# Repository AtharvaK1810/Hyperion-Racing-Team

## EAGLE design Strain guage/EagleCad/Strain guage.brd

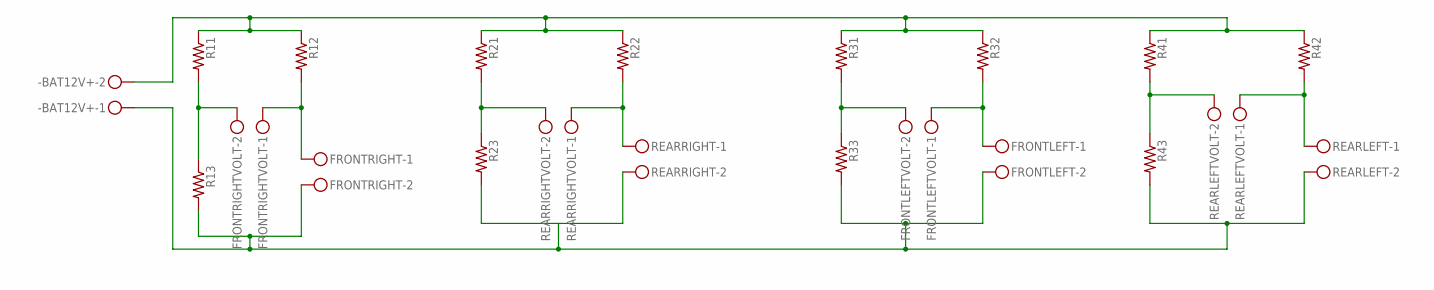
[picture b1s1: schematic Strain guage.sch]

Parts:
-BAT12V+: MKDSN1,5/2-5,08
FRONTLEFT: MKDSN1,5/2-5,08
FRONTLEFTVOLT: MKDSN1,5/2-5,08
FRONTRIGHT: MKDSN1,5/2-5,08
FRONTRIGHTVOLT: MKDSN1,5/2-5,08
R11, R12, R13, R21, R22, R23, R31, R32, R33, R41, R42, R43: R-US_0204/7; 0204/7
REARLEFT: MKDSN1,5/2-5,08
REARLEFTVOLT: MKDSN1,5/2-5,08
REARRIGHT: MKDSN1,5/2-5,08
REARRIGHTVOLT: MKDSN1,5/2-5,08

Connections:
unnamed: -BAT12V+.2, R11.1, R12.1, R21.1, R22.1, R31.1, R32.1, R41.1, R42.1
unnamed: FRONTRIGHTVOLT.2, R11.2, R13.1
unnamed: -BAT12V+.1, FRONTLEFT.2, FRONTRIGHT.2, R13.2, R23.2, R33.2, R43.2, REARLEFT.2, REARRIGHT.2
unnamed: FRONTRIGHT.1, FRONTRIGHTVOLT.1, R12.2
unnamed: R21.2, R23.1, REARRIGHTVOLT.2
unnamed: R22.2, REARRIGHT.1, REARRIGHTVOLT.1
unnamed: FRONTLEFTVOLT.2, R31.2, R33.1
unnamed: FRONTLEFT.1, FRONTLEFTVOLT.1, R32.2
unnamed: R41.2, R43.1, REARLEFTVOLT.2
unnamed: R42.2, REARLEFT.1, REARLEFTVOLT.1

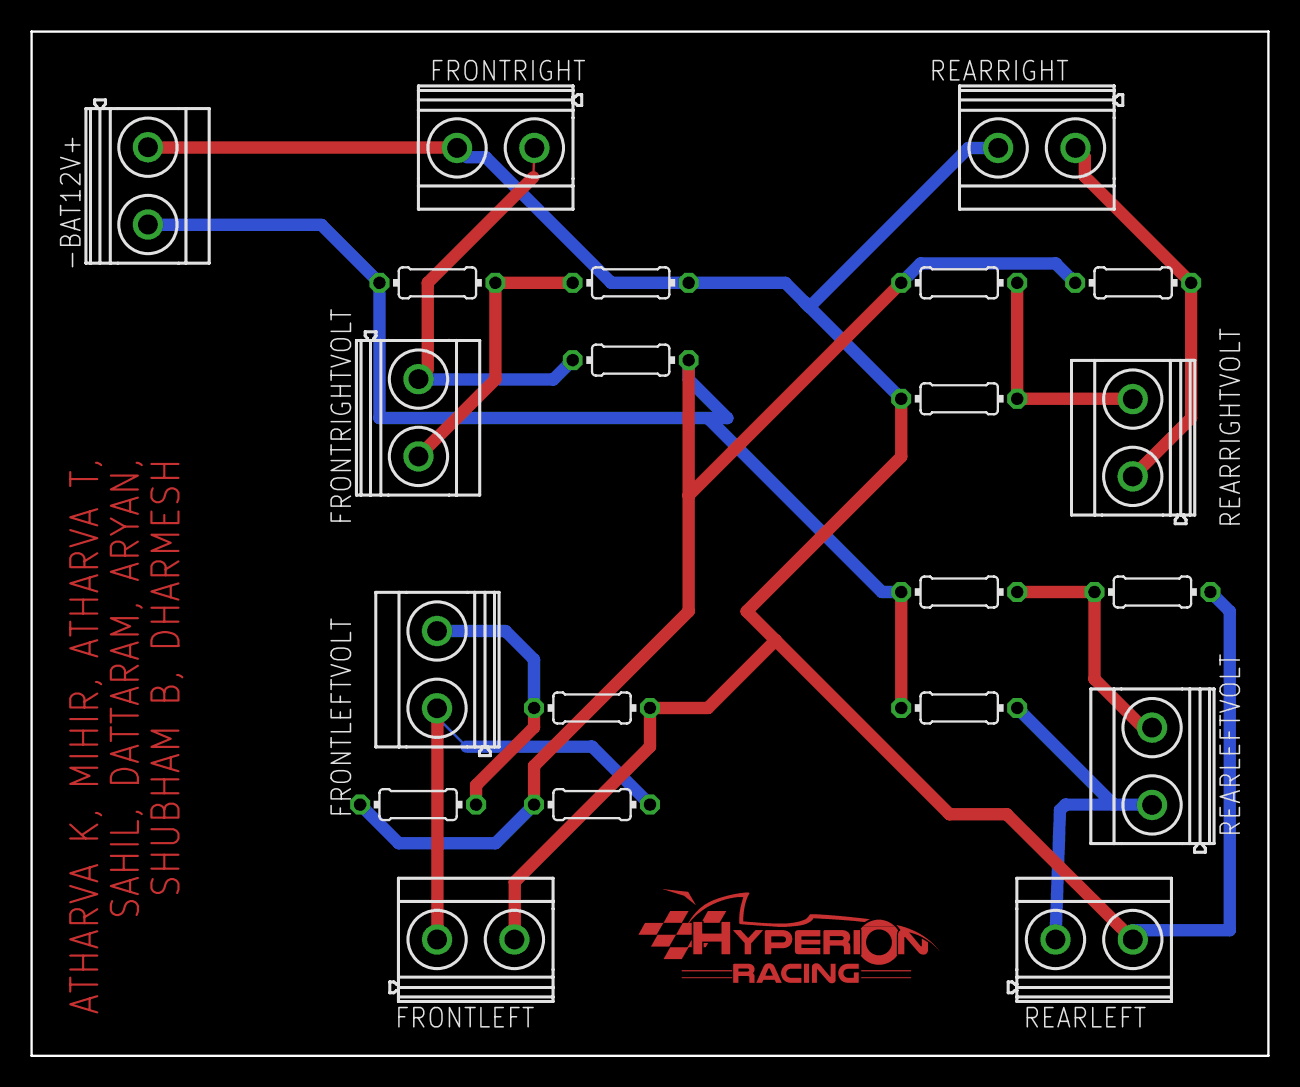
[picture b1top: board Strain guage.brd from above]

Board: 2 copper layers, 81.3 x 67.3 mm, 21 parts (0 on the bottom side), 10 nets.

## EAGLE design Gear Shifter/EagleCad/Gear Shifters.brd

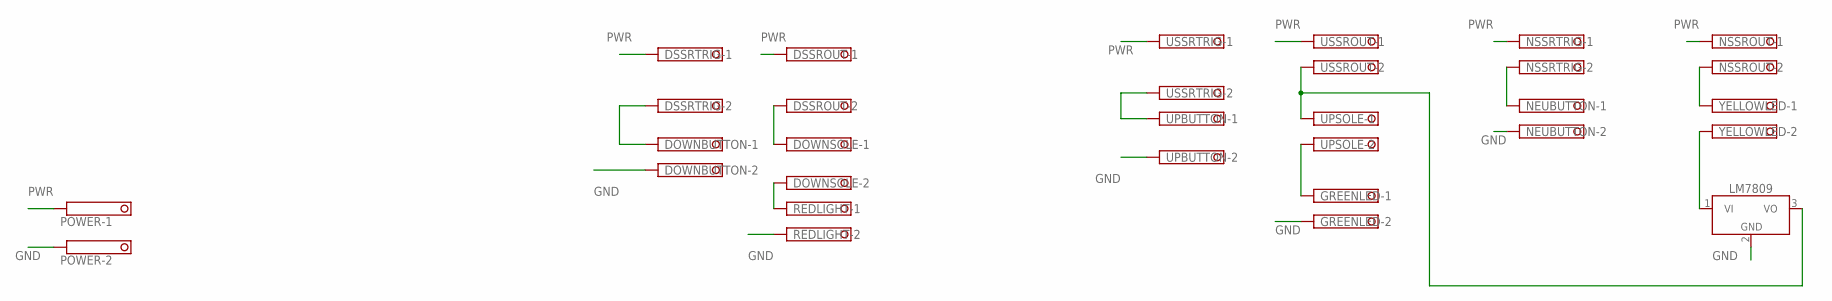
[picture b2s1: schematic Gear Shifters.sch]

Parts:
DOWNBUTTON: TERMINAL-BLOCK-3.5MM-2-PIN-ROUND-PAD; TERMINAL-BLOCK-2-PIN-3.5MM-ROUND-PAD
DOWNSOLE: TERMINAL-BLOCK-3.5MM-2-PIN-ROUND-PAD; TERMINAL-BLOCK-2-PIN-3.5MM-ROUND-PAD
DSSROUT: TERMINAL-BLOCK-3.5MM-2-PIN-ROUND-PAD; TERMINAL-BLOCK-2-PIN-3.5MM-ROUND-PAD
DSSRTRIG: TERMINAL-BLOCK-3.5MM-2-PIN-ROUND-PAD; TERMINAL-BLOCK-2-PIN-3.5MM-ROUND-PAD
GREENLED: TERMINAL-BLOCK-3.5MM-2-PIN-ROUND-PAD; TERMINAL-BLOCK-2-PIN-3.5MM-ROUND-PAD
LM7809: LM7805_TO220V; TO220V
NEUBUTTON: TERMINAL-BLOCK-3.5MM-2-PIN-ROUND-PAD; TERMINAL-BLOCK-2-PIN-3.5MM-ROUND-PAD
NSSROUT: TERMINAL-BLOCK-3.5MM-2-PIN-ROUND-PAD; TERMINAL-BLOCK-2-PIN-3.5MM-ROUND-PAD
NSSRTRIG: TERMINAL-BLOCK-3.5MM-2-PIN-ROUND-PAD; TERMINAL-BLOCK-2-PIN-3.5MM-ROUND-PAD
POWER: TERMINAL-BLOCK-3.5MM-2-PIN-ROUND-PAD; TERMINAL-BLOCK-2-PIN-3.5MM-ROUND-PAD
REDLIGHT: TERMINAL-BLOCK-3.5MM-2-PIN-ROUND-PAD; TERMINAL-BLOCK-2-PIN-3.5MM-ROUND-PAD
UPBUTTON: TERMINAL-BLOCK-3.5MM-2-PIN-ROUND-PAD; TERMINAL-BLOCK-2-PIN-3.5MM-ROUND-PAD
UPSOLE: TERMINAL-BLOCK-3.5MM-2-PIN-ROUND-PAD; TERMINAL-BLOCK-2-PIN-3.5MM-ROUND-PAD
USSROUT: TERMINAL-BLOCK-3.5MM-2-PIN-ROUND-PAD; TERMINAL-BLOCK-2-PIN-3.5MM-ROUND-PAD
USSRTRIG: TERMINAL-BLOCK-3.5MM-2-PIN-ROUND-PAD; TERMINAL-BLOCK-2-PIN-3.5MM-ROUND-PAD
YELLOWLED: TERMINAL-BLOCK-3.5MM-2-PIN-ROUND-PAD; TERMINAL-BLOCK-2-PIN-3.5MM-ROUND-PAD

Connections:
GND: DOWNBUTTON.2, GREENLED.2, LM7809.2 (GND), NEUBUTTON.2, POWER.2, REDLIGHT.2, UPBUTTON.2
unnamed: DOWNBUTTON.1, DSSRTRIG.2
unnamed: DOWNSOLE.1, DSSROUT.2
unnamed: UPBUTTON.1, USSRTRIG.2
unnamed: DOWNSOLE.2, REDLIGHT.1
unnamed: NEUBUTTON.1, NSSRTRIG.2
unnamed: NSSROUT.2, YELLOWLED.1
unnamed: LM7809.1 (VI), YELLOWLED.2
unnamed: LM7809.3 (VO), UPSOLE.1, USSROUT.2
unnamed: GREENLED.1, UPSOLE.2
PWR: DSSROUT.1, DSSRTRIG.1, NSSROUT.1, NSSRTRIG.1, POWER.1, USSROUT.1, USSRTRIG.1

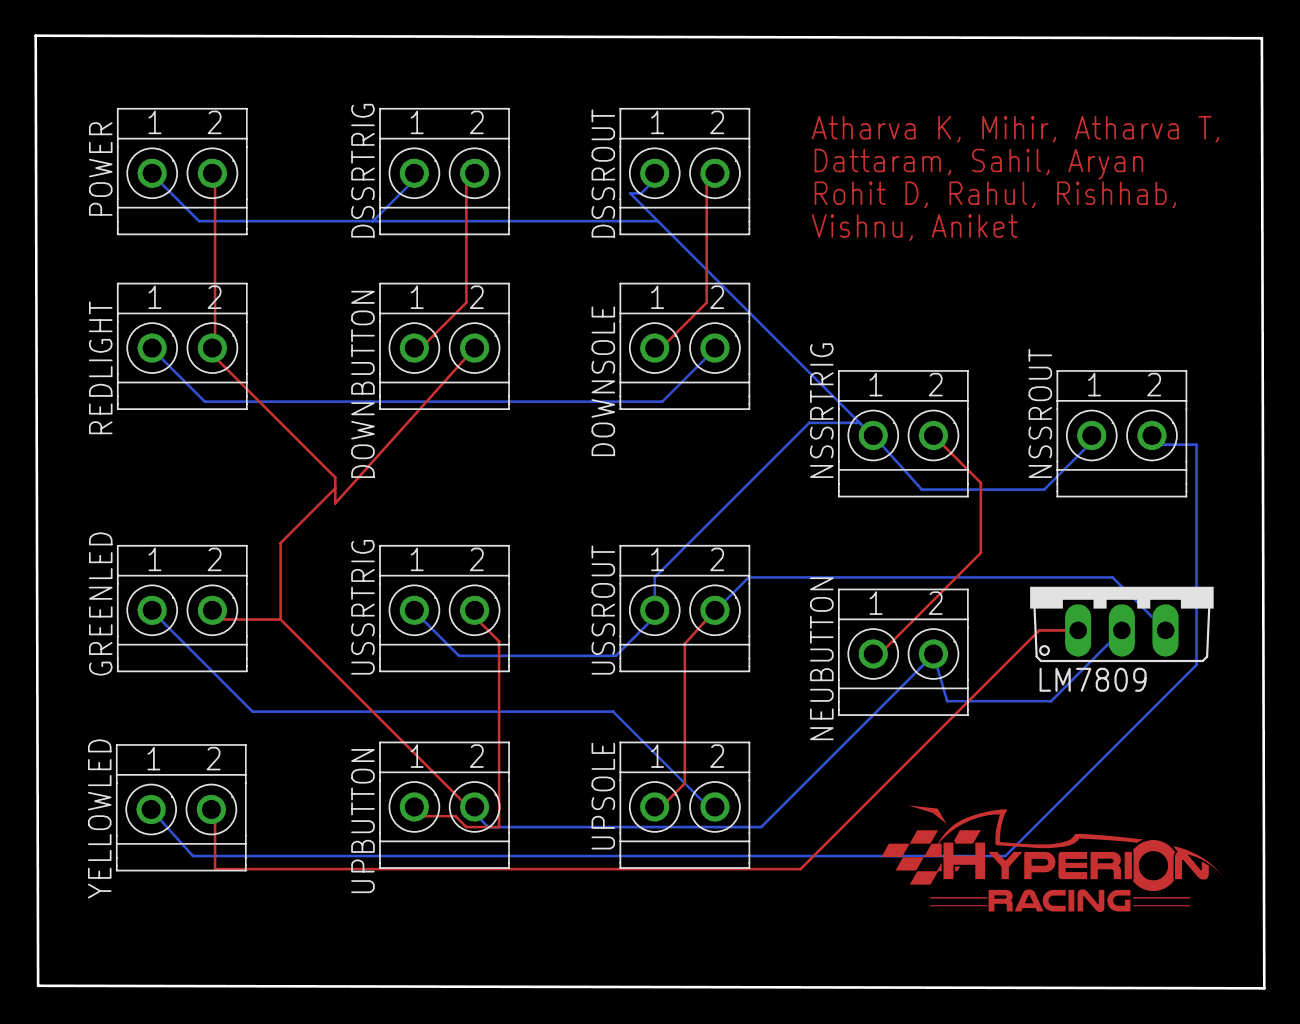
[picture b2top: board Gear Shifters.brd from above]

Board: 2 copper layers, 71.4 x 55.4 mm, 16 parts (0 on the bottom side), 11 nets.

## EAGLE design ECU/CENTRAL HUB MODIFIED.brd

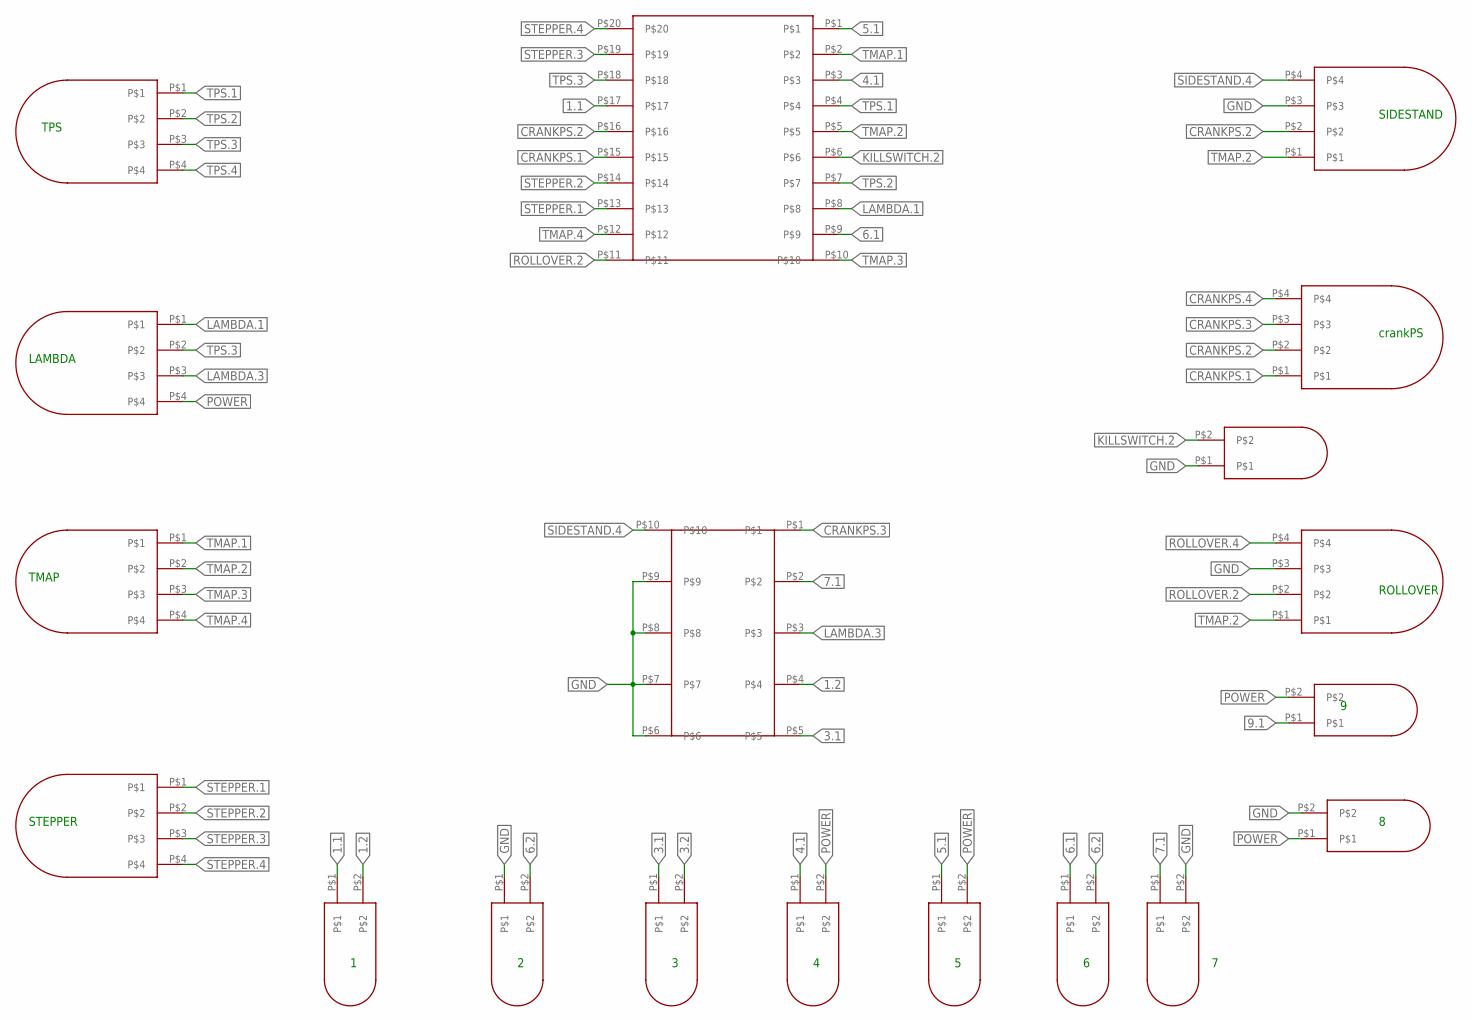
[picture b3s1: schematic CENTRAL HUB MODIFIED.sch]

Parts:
1, 2, 3, 4, 5, 6, 7, 8, 9: 2-PIN; 2PIN
CRANK: 4-PIN; 4PIN
KILLSWITCH: 2-PIN; 2PIN
LAMBDA: 4-PIN; 4PIN
ROLLOVER: 4-PIN; 4PIN
SIDESTAND: 4-PIN; 4PIN
STEPPER: 4-PIN; 4PIN
TMAP: 4-PIN; 4PIN
TPS: 4-PIN; 4PIN
U$1: ECU1-20; ECU
U$2: ECU2-10; 10PIN

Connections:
1.1: 1.P$1, U$1.P$17
1.2: 1.P$2, U$2.P$4
3.1: 3.P$1, U$2.P$5
3.2: 3.P$2
4.1: 4.P$1, U$1.P$3
5.1: 5.P$1, U$1.P$1
6.1: 6.P$1, U$1.P$9
6.2: 2.P$2, 6.P$2
7.1: 7.P$1, U$2.P$2
9.1: 9.P$1
CRANKPS.1: CRANK.P$1, U$1.P$15
CRANKPS.2: CRANK.P$2, SIDESTAND.P$2, U$1.P$16
CRANKPS.3: CRANK.P$3, U$2.P$1
CRANKPS.4: CRANK.P$4
GND: 2.P$1, 7.P$2, 8.P$2, KILLSWITCH.P$1, ROLLOVER.P$3, SIDESTAND.P$3, U$2.P$6, U$2.P$7, U$2.P$8, U$2.P$9
KILLSWITCH.2: KILLSWITCH.P$2, U$1.P$6
LAMBDA.1: LAMBDA.P$1, U$1.P$8
LAMBDA.3: LAMBDA.P$3, U$2.P$3
POWER: 4.P$2, 5.P$2, 8.P$1, 9.P$2, LAMBDA.P$4
ROLLOVER.2: ROLLOVER.P$2, U$1.P$11
ROLLOVER.4: ROLLOVER.P$4
SIDESTAND.4: SIDESTAND.P$4, U$2.P$10
STEPPER.1: STEPPER.P$1, U$1.P$13
STEPPER.2: STEPPER.P$2, U$1.P$14
STEPPER.3: STEPPER.P$3, U$1.P$19
STEPPER.4: STEPPER.P$4, U$1.P$20
TMAP.1: TMAP.P$1, U$1.P$2
TMAP.2: ROLLOVER.P$1, SIDESTAND.P$1, TMAP.P$2, U$1.P$5
TMAP.3: TMAP.P$3, U$1.P$10
TMAP.4: TMAP.P$4, U$1.P$12
TPS.1: TPS.P$1, U$1.P$4
TPS.2: TPS.P$2, U$1.P$7
TPS.3: LAMBDA.P$2, TPS.P$3, U$1.P$18
TPS.4: TPS.P$4

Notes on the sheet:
TPS
LAMBDA
TMAP
STEPPER
SIDESTAND
crankPS
ROLLOVER

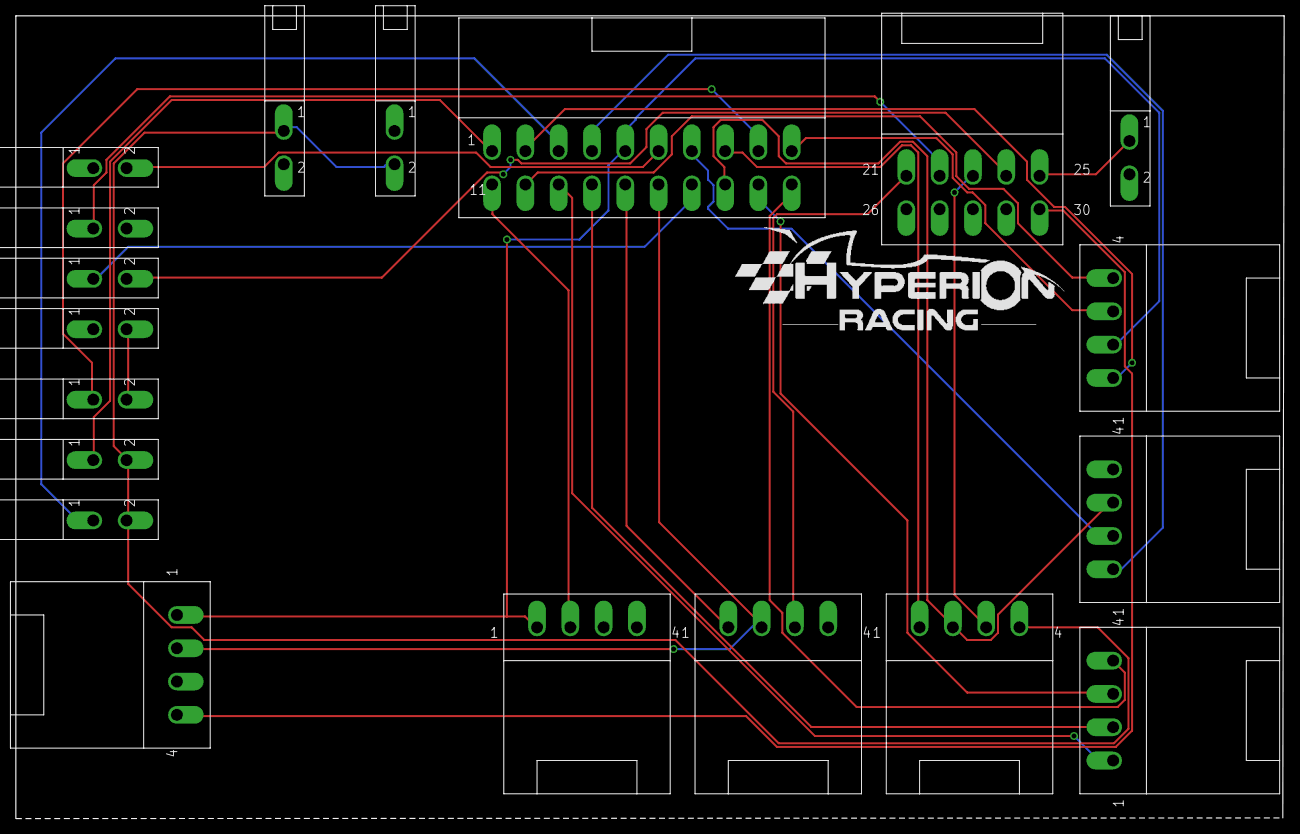
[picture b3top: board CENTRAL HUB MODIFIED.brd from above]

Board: 2 copper layers, 160.0 x 101.3 mm, 19 parts (0 on the bottom side), 29 nets.

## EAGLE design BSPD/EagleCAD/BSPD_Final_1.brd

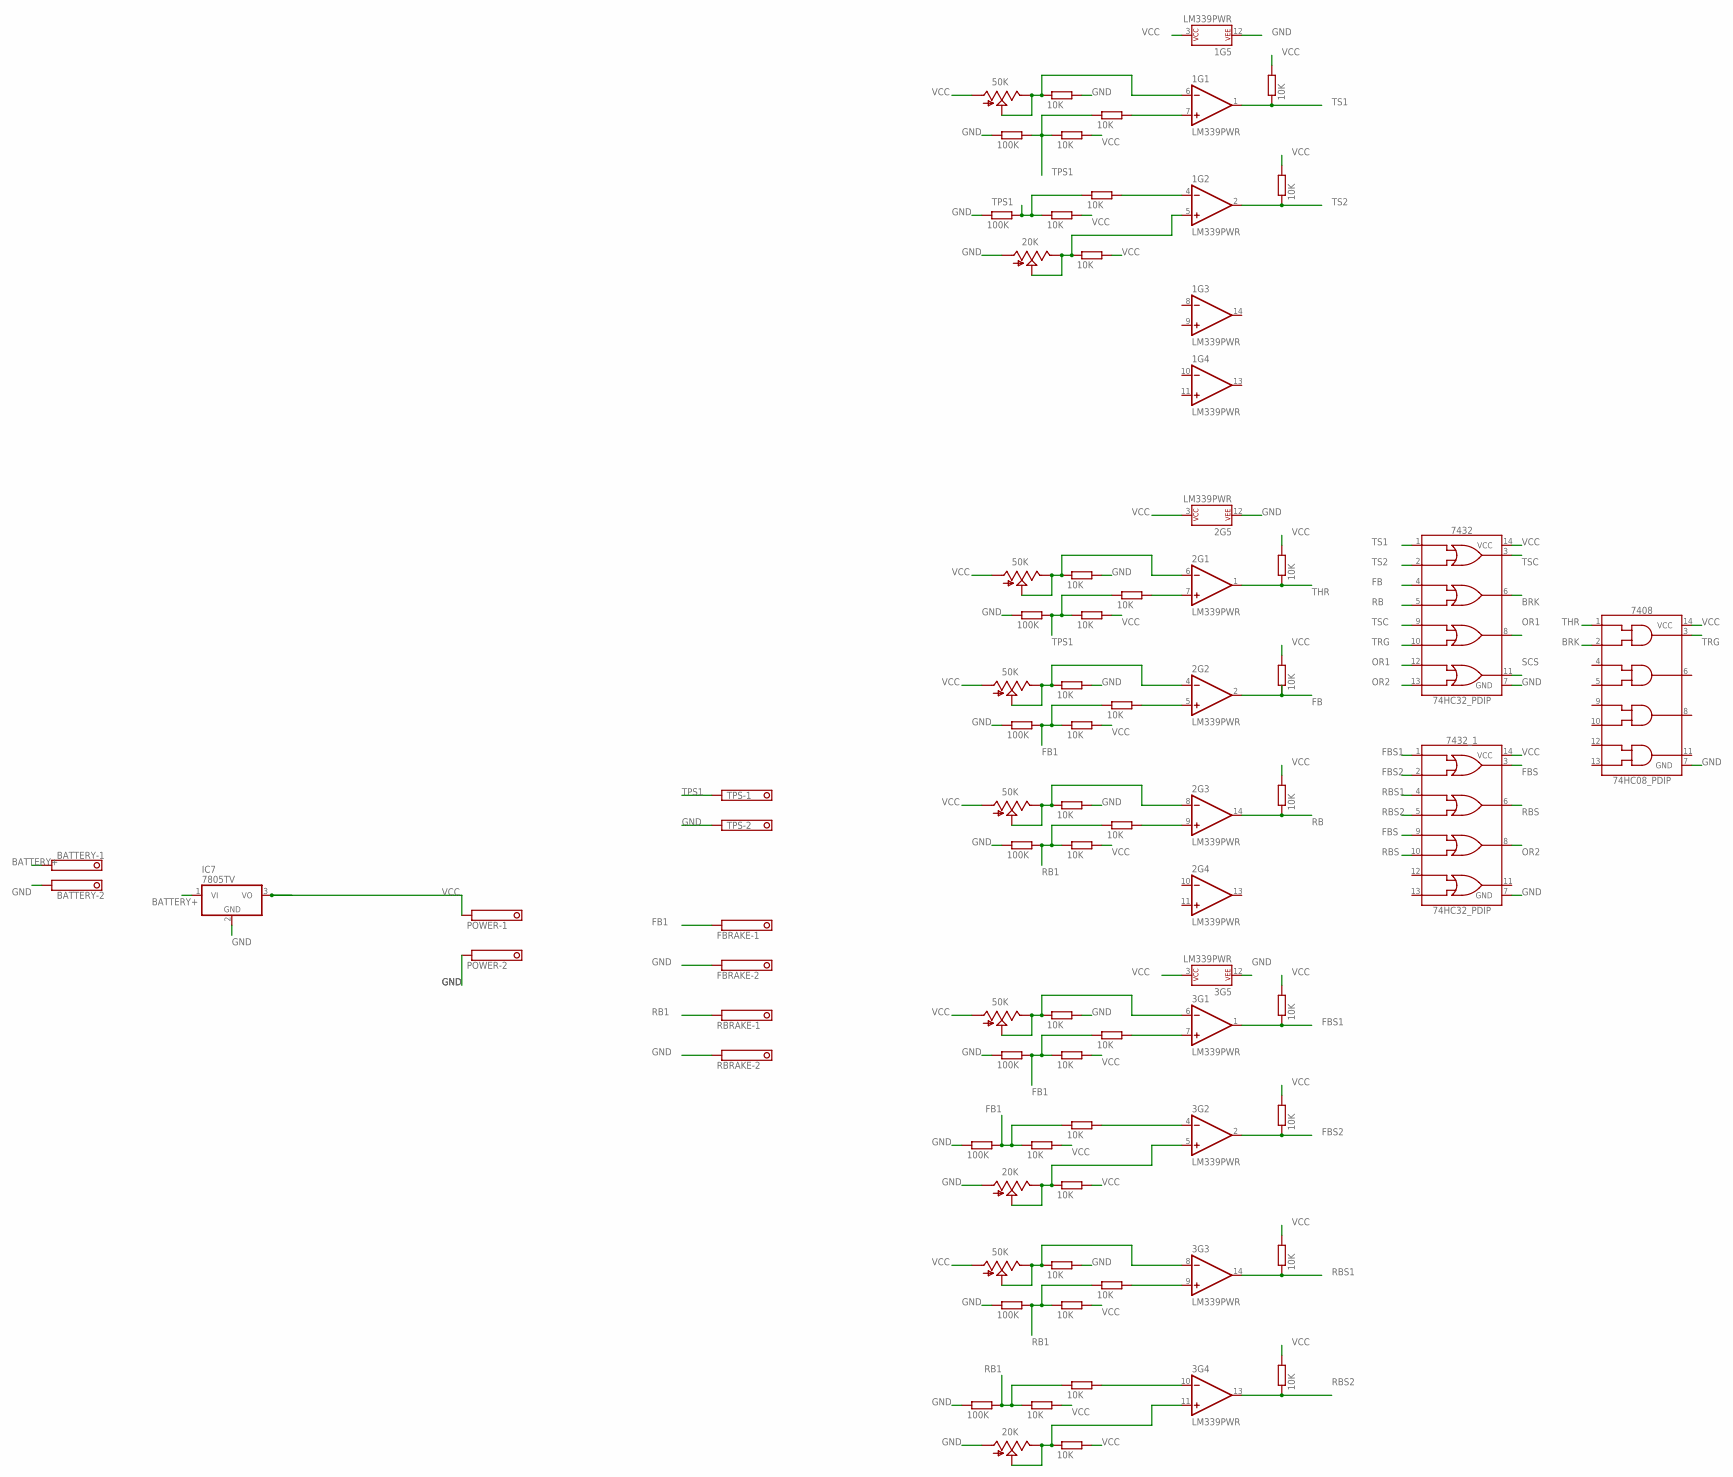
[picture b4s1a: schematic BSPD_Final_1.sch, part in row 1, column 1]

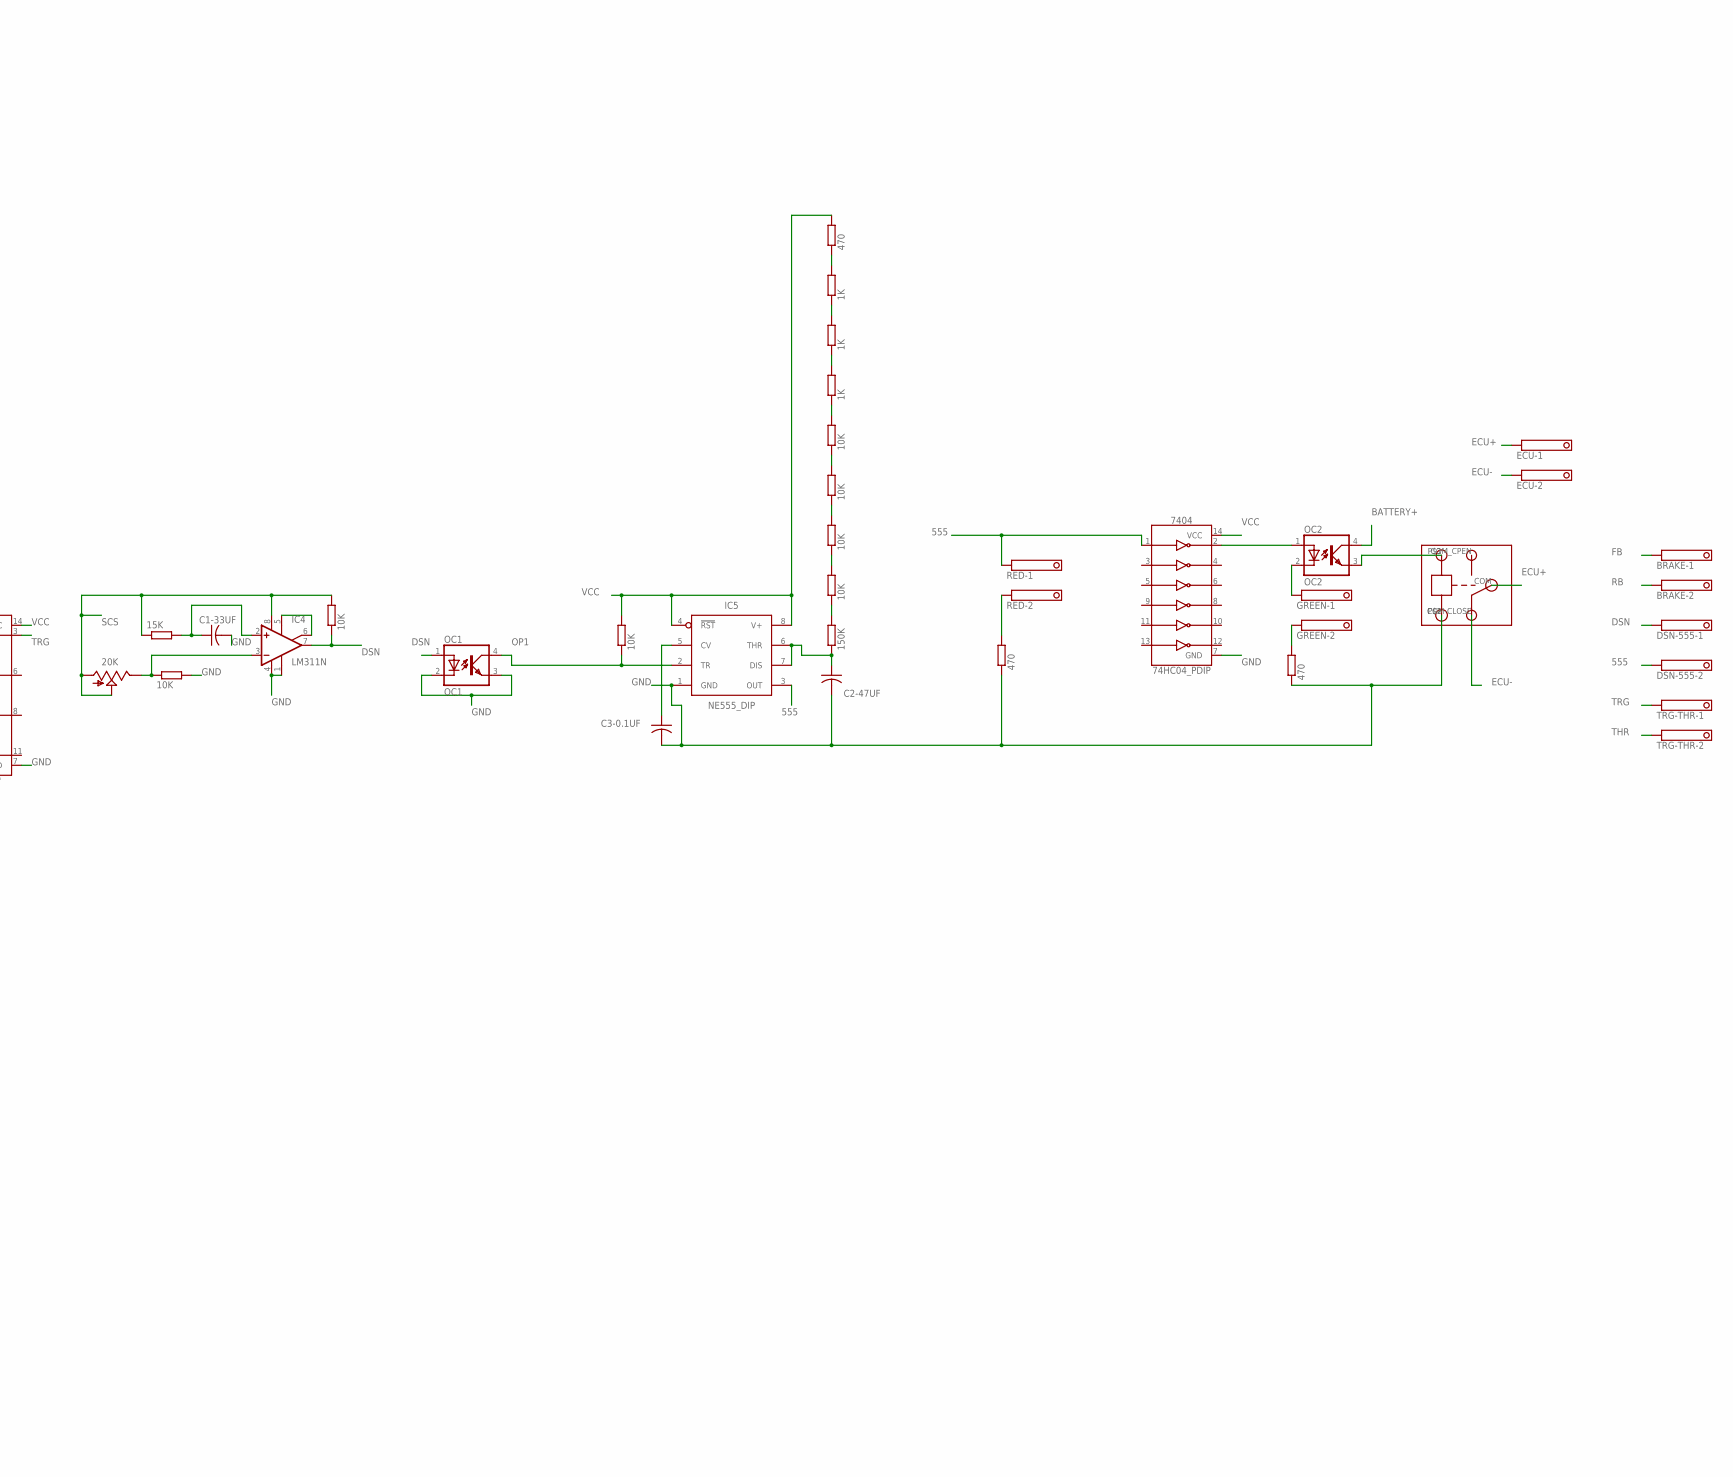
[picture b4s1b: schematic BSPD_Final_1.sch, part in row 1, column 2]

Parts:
1, 2, 3: LM339PWR; TSSOP-14
50K9: 20K; B64Y
555RES1: 150K; 0207/10
555RES2, 555RES3, 555RES4, 555RES5: 10K; 0207/10
555RES6, 555RES7, 555RES8: 1K; 0207/10
555RES9: 470; 0207/10
7404: 74HC04_PDIP; DIP762W53P254L1969H508Q14B
7408: 74HC08_PDIP; DIP762W53P254L1969H508Q14B
7432, 7432_1: 74HC32_PDIP; DIP762W53P254L1969H508Q14B
BATTERY: TERMINAL-BLOCK-3.5MM-2-PIN-ROUND-PAD; TERMINAL-BLOCK-2-PIN-3.5MM-ROUND-PAD
BRAKE: TERMINAL-BLOCK-3.5MM-2-PIN-ROUND-PAD; TERMINAL-BLOCK-2-PIN-3.5MM-ROUND-PAD
C1-33UF, C2-47UF, C3-0.1UF: 33uF; CAP_RADIAL_2MM
DCNPULL: 10K; 0207/10
DCNRES1: 15K; 0207/10
DCNRES2: 10K; 0207/10
DSN-555: TERMINAL-BLOCK-3.5MM-2-PIN-ROUND-PAD; TERMINAL-BLOCK-2-PIN-3.5MM-ROUND-PAD
ECU: TERMINAL-BLOCK-3.5MM-2-PIN-ROUND-PAD; TERMINAL-BLOCK-2-PIN-3.5MM-ROUND-PAD
FBRAKE: TERMINAL-BLOCK-3.5MM-2-PIN-ROUND-PAD; TERMINAL-BLOCK-2-PIN-3.5MM-ROUND-PAD
GREEN: TERMINAL-BLOCK-3.5MM-2-PIN-ROUND-PAD; TERMINAL-BLOCK-2-PIN-3.5MM-ROUND-PAD
IC4: LM311N; DIL08
IC5: NE555_DIP; DIP826W53P254L959H508Q8B
IC7: 7805TV; TO220V
OC1: OC1; DIL04
OC2: OC2; DIL04
OCTPULL: 10K; 0207/10
POT1, POT3, POT4, POT5, POT6, POT8: 50K; B64Y
POT2, POT7, POT9: 20K; B64Y
POWER: TERMINAL-BLOCK-3.5MM-2-PIN-ROUND-PAD; TERMINAL-BLOCK-2-PIN-3.5MM-ROUND-PAD
PULL1, PULL2, PULL3, PULL4, PULL5, PULL6, PULL7, PULL8, PULL9: 10K; 0207/10
R56, R57: 470; 0207/10
RBRAKE: TERMINAL-BLOCK-3.5MM-2-PIN-ROUND-PAD; TERMINAL-BLOCK-2-PIN-3.5MM-ROUND-PAD
RED: TERMINAL-BLOCK-3.5MM-2-PIN-ROUND-PAD; TERMINAL-BLOCK-2-PIN-3.5MM-ROUND-PAD
RES11, RES12, RES14, RES21, RES22, RES23, RES31, RES32, RES34, RES41, RES42, RES44, RES51, RES52, RES54, RES61, RES62, RES64, RES71, RES72, RES74, RES81, RES82, RES84, RES91, RES92, RES94: 10K; 0207/10
RES13, RES24, RES33, RES43, RES53, RES63, RES73, RES83, RES93: 100K; 0207/10
TPS: TERMINAL-BLOCK-3.5MM-2-PIN-ROUND-PAD; TERMINAL-BLOCK-2-PIN-3.5MM-ROUND-PAD
TRG-THR: TERMINAL-BLOCK-3.5MM-2-PIN-ROUND-PAD; TERMINAL-BLOCK-2-PIN-3.5MM-ROUND-PAD
U$1: RELAY

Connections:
555: 7404.1 (1A), DSN-555.2, IC5.3 (OUT), RED.1
BATTERY+: BATTERY.1, IC7.1 (VI), OC2.4 (COL)
BRK: 7408.2 (1B), 7432.6 (2Y)
DSN: DCNPULL.1, DSN-555.1, IC4.7 (OUT), OC1.1 (A)
ECU+: ECU.1, U$1.COM
ECU-: ECU.2, U$1.COM-CLOSE
FB: 2.2 (OUT), 7432.4 (2A), BRAKE.1, PULL4.1
FB1: FBRAKE.1, RES41.1, RES42.1, RES43.2, RES61.1, RES62.1, RES63.2, RES71.1, RES72.1, RES73.2
FBS: 7432_1.3 (1Y), 7432_1.9 (3A)
FBS1: 3.1 (OUT), 7432_1.1 (1A), PULL6.1
FBS2: 3.2 (OUT), 7432_1.2 (1B), PULL7.1
GND: 1.12 (P$V-), 2.12 (P$V-), 3.12 (P$V-), 7404.7 (GND), 7408.7 (GND), 7432.7 (GND), 7432_1.7 (GND), BATTERY.2, C1-33UF.2, C2-47UF.2, C3-0.1UF.2, DCNRES2.2, FBRAKE.2, IC4.1 (GND), IC4.4 (V-), IC5.1 (GND), IC7.2 (GND), OC1.2 (C), OC1.3 (EMIT), POT2.A, POT7.A, POT9.A, POWER.2, R56.1, R57.1, RBRAKE.2, RES13.1, RES14.2, RES24.1, RES33.1, RES34.2, RES43.1, RES44.2, RES53.1, RES54.2, RES63.1, RES64.2, RES73.1, RES83.1, RES84.2, RES93.1, TPS.2, U$1.P$2 (GND)
unnamed: 2.7 (+IN), RES31.2
unnamed: IC4.5 (ON), IC4.6 (ON/STR)
unnamed: 2.6 (-IN), POT3.E, POT3.S, RES34.1
unnamed: 2.5 (+IN), RES41.2
unnamed: 2.4 (-IN), POT4.E, POT4.S, RES44.1
unnamed: R56.2, RED.2
unnamed: 2.9 (+IN), RES51.2
unnamed: 2.8 (-IN), POT5.E, POT5.S, RES54.1
unnamed: C1-33UF.1, DCNRES1.2, IC4.2 (+IN)
unnamed: 3.7 (+IN), RES61.2
unnamed: 3.6 (-IN), POT6.E, POT6.S, RES64.1
unnamed: 50K9.E, DCNRES2.1, IC4.3 (-IN)
unnamed: 3.9 (+IN), RES81.2
unnamed: 3.8 (-IN), POT8.E, POT8.S, RES84.1
unnamed: C3-0.1UF.1, IC5.5 (CV)
unnamed: 1.7 (+IN), RES11.2
unnamed: 1.6 (-IN), POT1.E, POT1.S, RES14.1
unnamed: 1.4 (-IN), RES21.2
unnamed: 1.5 (+IN), POT2.E, POT2.S, RES23.1
unnamed: 555RES1.2, 555RES2.1
unnamed: 3.4 (-IN), RES71.2
unnamed: 555RES2.2, 555RES3.1
unnamed: 3.5 (+IN), POT7.E, POT7.S, RES74.1
unnamed: 555RES3.2, 555RES4.1
unnamed: 3.10 (-IN), RES91.2
unnamed: 555RES4.2, 555RES5.1
unnamed: 3.11 (+IN), POT9.E, POT9.S, RES94.1
unnamed: 555RES5.2, 555RES6.1
unnamed: GREEN.2, R57.2
unnamed: 7404.2 (1Y), OC2.1 (A)
unnamed: GREEN.1, OC2.2 (C)
unnamed: OC2.3 (EMIT), U$1.P$1 (IN)
unnamed: 555RES8.2, 555RES9.1
unnamed: 555RES7.2, 555RES8.1
unnamed: 555RES6.2, 555RES7.1
unnamed: 555RES1.1, C2-47UF.1, IC5.6 (THR), IC5.7 (DIS)
OP1: IC5.2 (TR), OC1.4 (COL), OCTPULL.1
OR1: 7432.8 (3Y), 7432.12 (4A)
OR2: 7432.13 (4B), 7432_1.8 (3Y)
RB: 2.14 (OUT), 7432.5 (2B), BRAKE.2, PULL5.1
RB1: RBRAKE.1, RES51.1, RES52.1, RES53.2, RES81.1, RES82.1, RES83.2, RES91.1, RES92.1, RES93.2
RBS: 7432_1.6 (2Y), 7432_1.10 (3B)
RBS1: 3.14 (OUT), 7432_1.4 (2A), PULL8.1
RBS2: 3.13 (OUT), 7432_1.5 (2B), PULL9.1
SCS: 50K9.A, 50K9.S, 7432.11 (4Y), DCNPULL.2, DCNRES1.1, IC4.8 (V+)
THR: 2.1 (OUT), 7408.1 (1A), PULL3.1, TRG-THR.2
TPS1: RES11.1, RES12.1, RES13.2, RES21.1, RES22.1, RES24.2, RES31.1, RES32.1, RES33.2, TPS.1
TRG: 7408.3 (1Y), 7432.10 (3B), TRG-THR.1
TS1: 1.1 (OUT), 7432.1 (1A), PULL1.1
TS2: 1.2 (OUT), 7432.2 (1B), PULL2.1
TSC: 7432.3 (1Y), 7432.9 (3A)
VCC: 1.3 (P$V+), 2.3 (P$V+), 3.3 (P$V+), 555RES9.2, 7404.14 (VCC), 7408.14 (VCC), 7432.14 (VCC), 7432_1.14 (VCC), IC5.4 (!RST), IC5.8 (V+), IC7.3 (VO), OCTPULL.2, POT1.A, POT3.A, POT4.A, POT5.A, POT6.A, POT8.A, POWER.1, PULL1.2, PULL2.2, PULL3.2, PULL4.2, PULL5.2, PULL6.2, PULL7.2, PULL8.2, PULL9.2, RES12.2, RES22.2, RES23.2, RES32.2, RES42.2, RES52.2, RES62.2, RES72.2, RES74.2, RES82.2, RES92.2, RES94.2

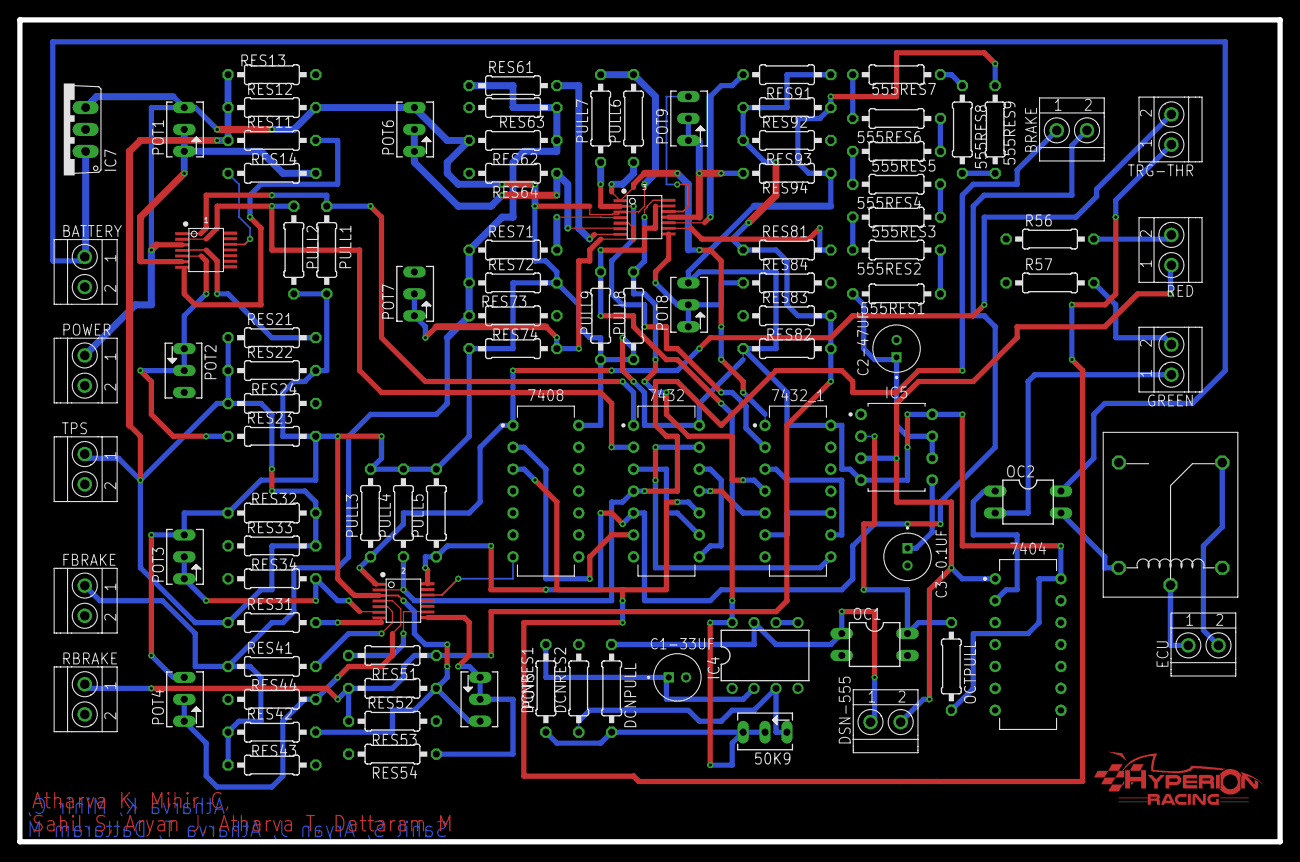
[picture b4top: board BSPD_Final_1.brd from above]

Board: 2 copper layers, 146.1 x 95.2 mm, 97 parts (0 on the bottom side), 64 nets.

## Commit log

2025-11-23 Create temp
2025-11-23 Photo
2025-11-23 Rename Photo to Photo.jpeg
2025-11-23 Create Tem
2025-11-23 Create T

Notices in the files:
parts and their libraries:
SparkFun-IC-Amplifiers: Licensing: Creative Commons ShareAlike 4.0 International - https://creativecommons.org/licenses/by-sa/4.0
